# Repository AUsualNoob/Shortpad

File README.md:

# Shortpad:
The shortpad is a 5 Key macropad that uses KMK for software

# Features:
- 0.91" OLED display
- 4 Keys for shortcuts
- 1 Key to display what each key does via the OLED
- Utilizes the XIAO RP2040 for firmware

# PCB

## Schematic:

## PCB:

I regret not adding a ground plane, I didn't even use any traces on the bottom

# CAD:

Made with Fusion360, idk what else to add honestly

# Firmware overview:
The firmware was made using KMK and CircuitPython

# BOM:
- 1x XIAO RP2040
- 5x Cherry MX Switches
- 4x M3x5x4 Heatset inserts
- 1x 0.91" 128x32 OLED Display
- 1x Case (2x 3D Printed parts)

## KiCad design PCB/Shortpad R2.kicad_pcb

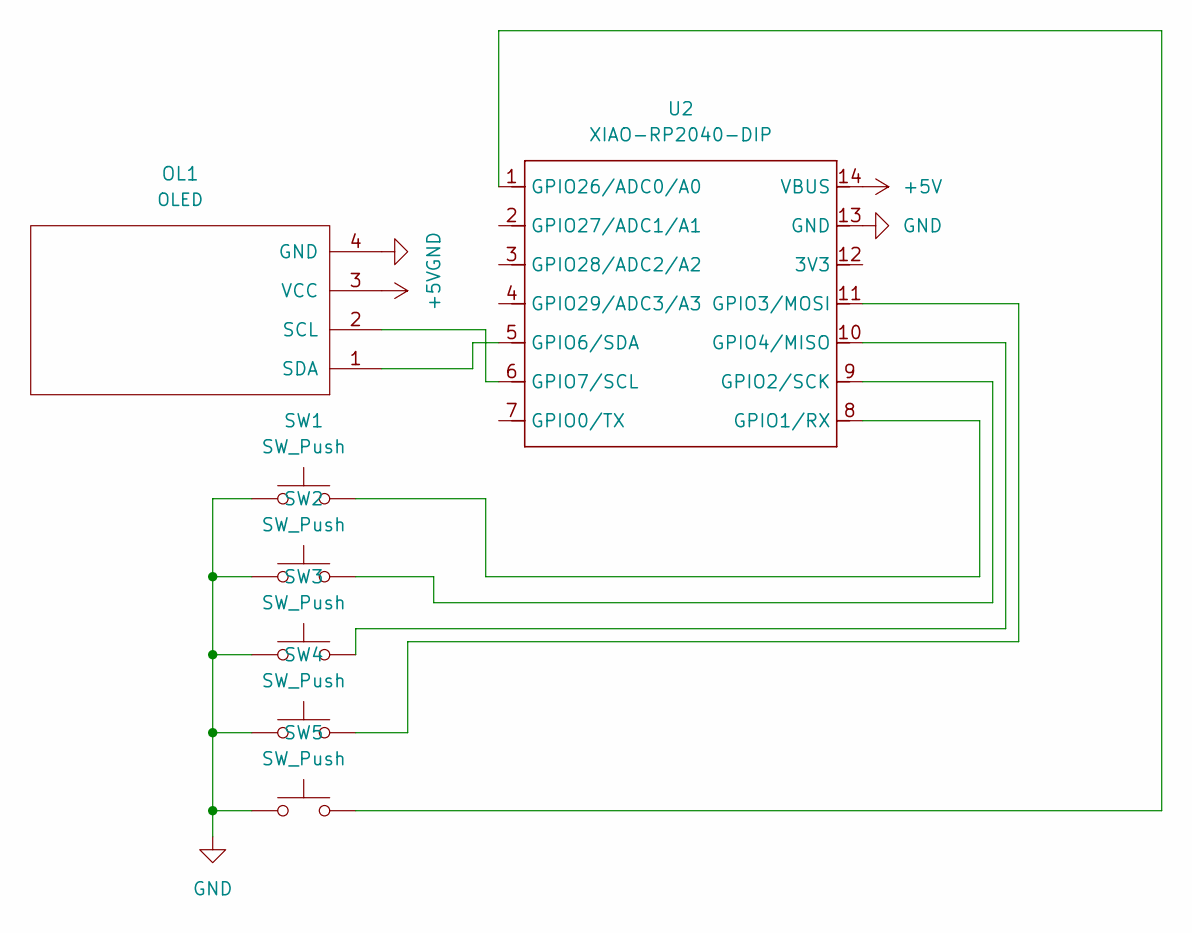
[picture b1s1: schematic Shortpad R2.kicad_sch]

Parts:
OL1: OLED; OLED_v2
SW1, SW2, SW3, SW4, SW5: SW_Push; SW_Cherry_MX_1.00u_PCB
U2: XIAO-RP2040-DIP

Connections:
+5V: OL1.3 (VCC), U2.14 (VBUS)
GND: OL1.4 (GND), SW1.1, SW2.1, SW3.1, SW4.1, SW5.1, U2.13 (GND)
unnamed: OL1.2 (SCL), U2.6 (GPIO7/SCL)
unnamed: OL1.1 (SDA), U2.5 (GPIO6/SDA)
unnamed: SW1.2, U2.8 (GPIO1/RX)
unnamed: SW2.2, U2.9 (GPIO2/SCK)
unnamed: SW4.2, U2.11 (GPIO3/MOSI)
unnamed: SW3.2, U2.10 (GPIO4/MISO)
unnamed: SW5.2, U2.1 (GPIO26/ADC0/A0)

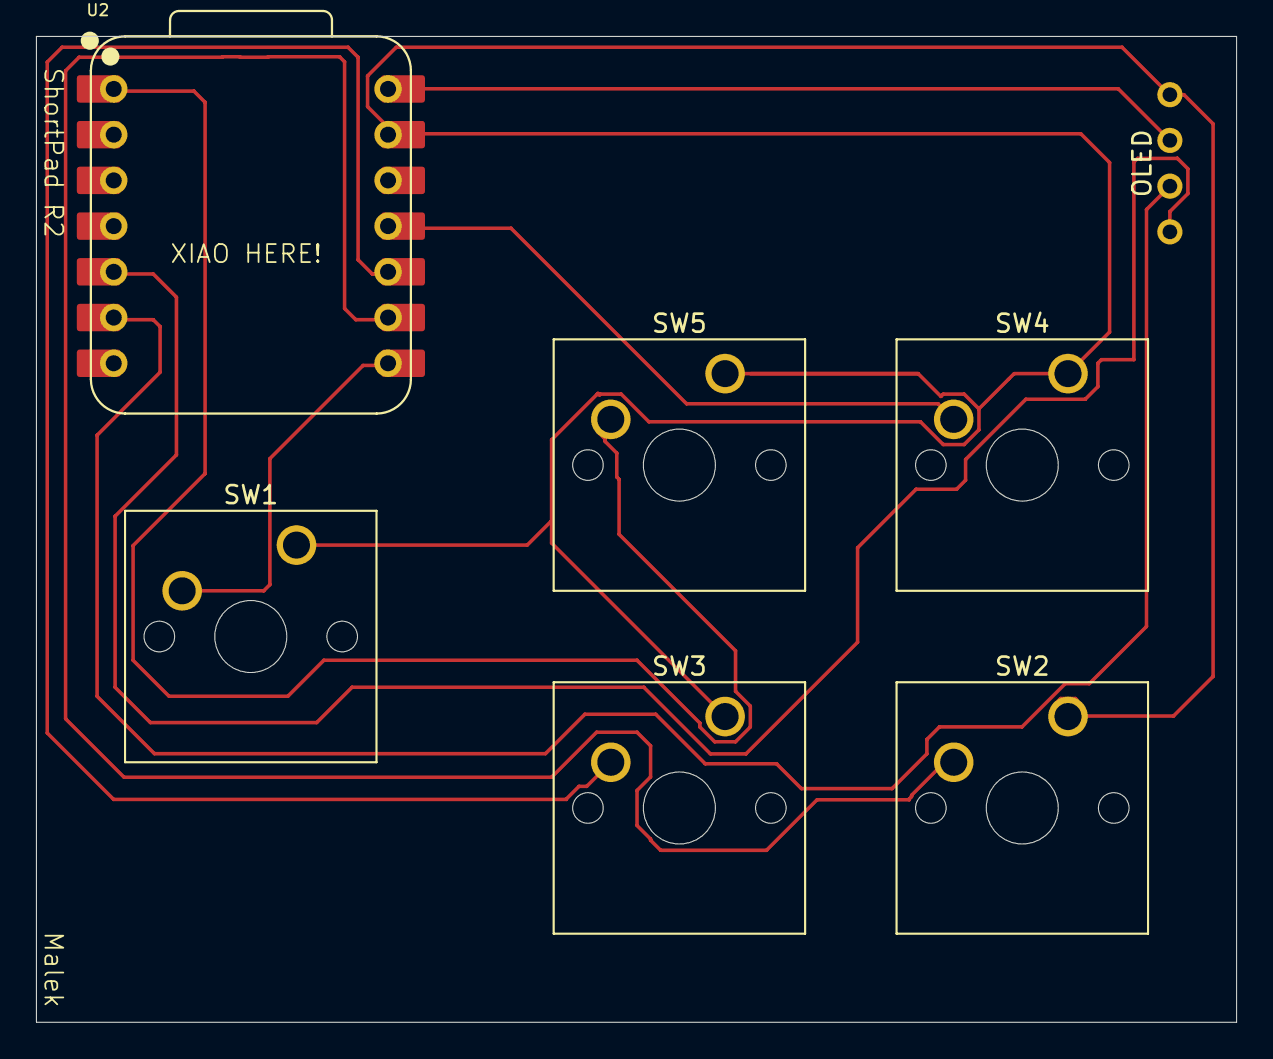
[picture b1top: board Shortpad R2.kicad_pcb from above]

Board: 2 copper layers, 66.7 x 54.8 mm, 7 parts (0 on the bottom side), 9 nets.

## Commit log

2026-03-18 Create Firmware
